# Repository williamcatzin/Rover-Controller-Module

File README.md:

# **Rover Controller Module**

The Rover Controller Module is an electronic control module (ECM) for a Mars rover prototype being developed by the AI Rover team from the Space Technologies At Cal (STAC). The PCB is a four-layer board consisting of an ESP32-WROOM32 module, BMI088 IMU breakout board, RFM69HCW transceiver module, UART header pin interface for three Roboclaw 2x7A motor controllers, and a SPI header pin interface for an external microprocessor such as an NVIDIA Jetson or Raspberry Pi. There’s also decoupling capacitors to suppress power supply noise and TVS diodes for safety and component protection. The PCB was designed using KiCAD and manufactured by JLCPCB. Top and bottom layers are signal planes. First middle layer is the ground plane and the second middle layer is the power plane. I've also placed three test points at the UART, I2C, and SPI serial buses respectively, mounting holes, and logos for aesthetics. Here’s the Rover Controller Module v1.

|||
|:-:|:-:|
|||

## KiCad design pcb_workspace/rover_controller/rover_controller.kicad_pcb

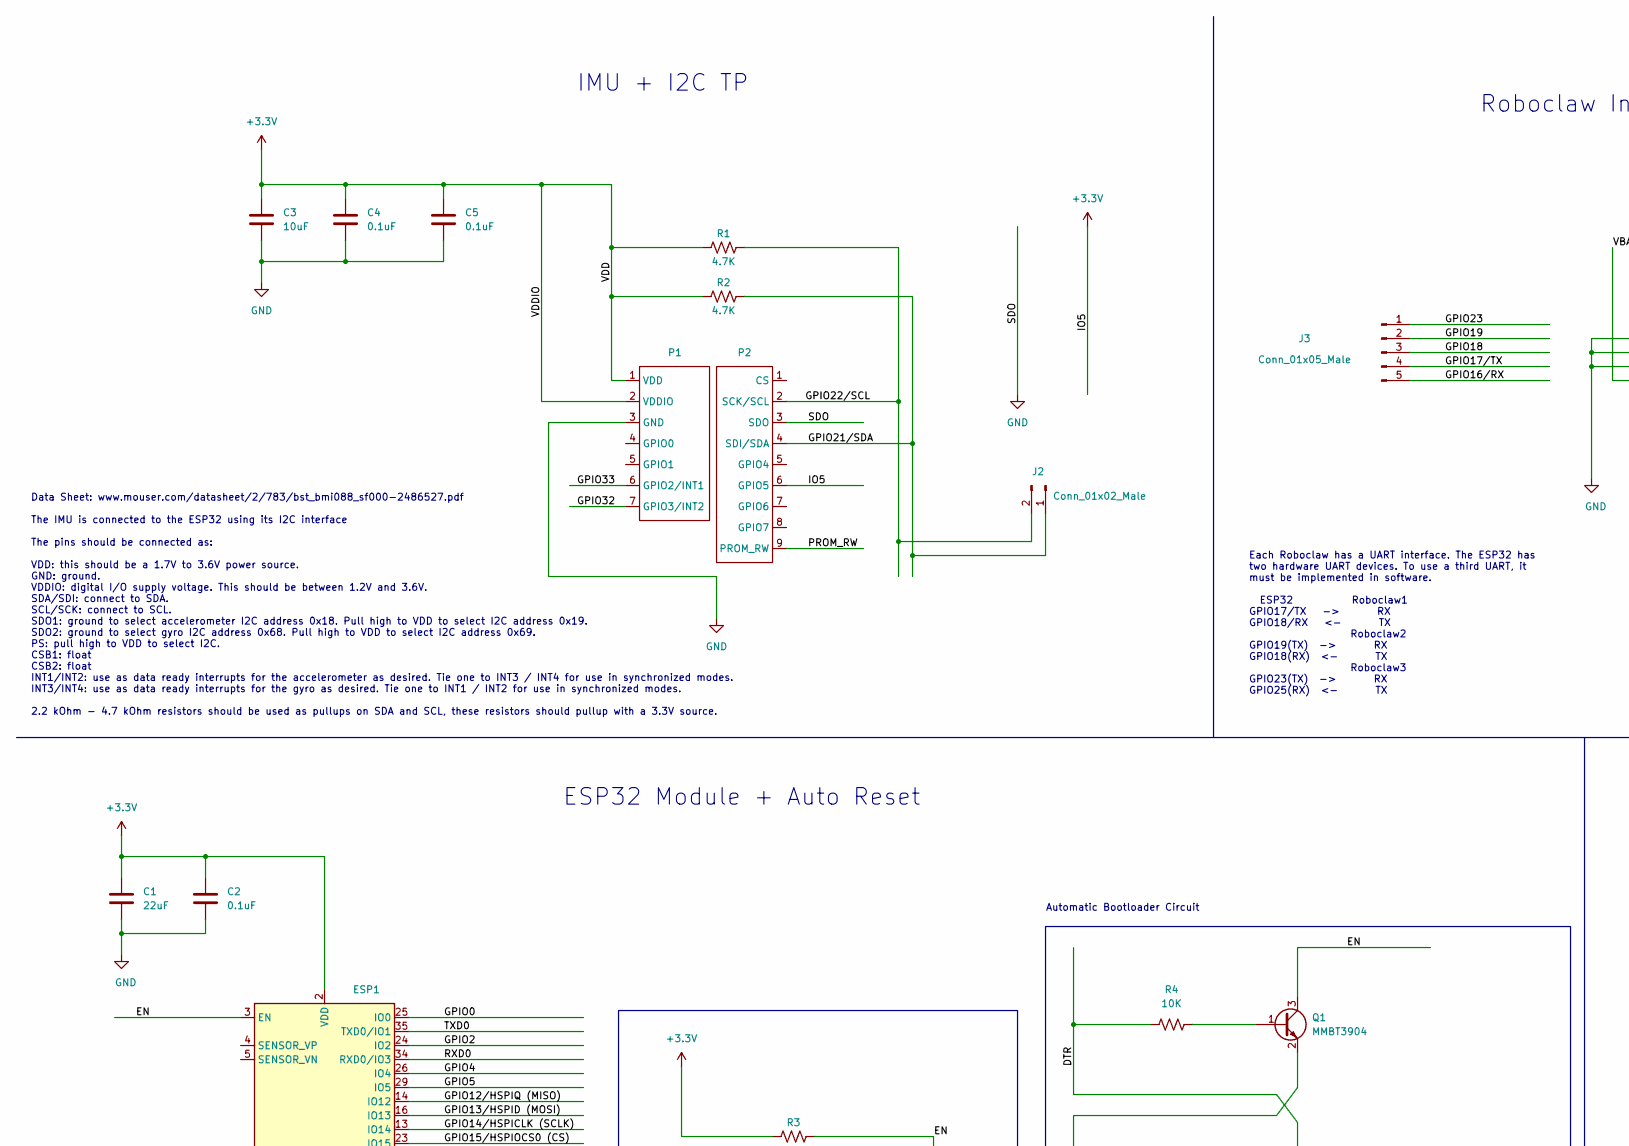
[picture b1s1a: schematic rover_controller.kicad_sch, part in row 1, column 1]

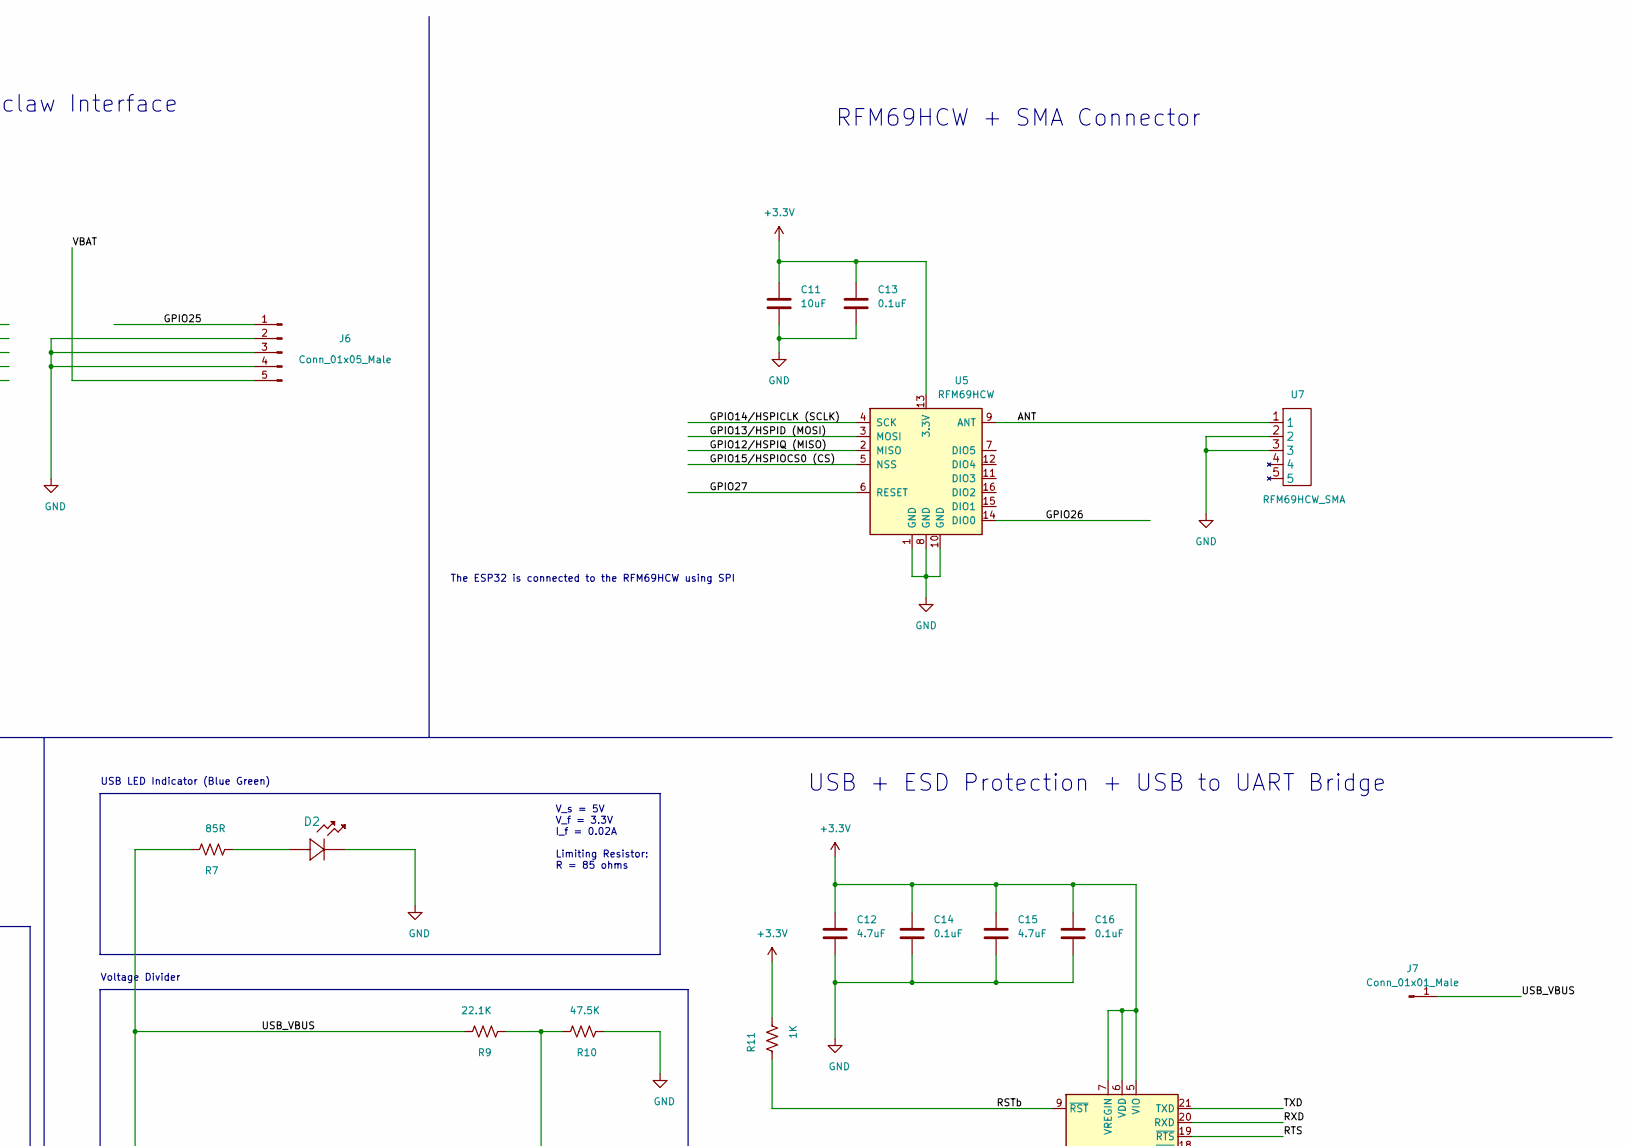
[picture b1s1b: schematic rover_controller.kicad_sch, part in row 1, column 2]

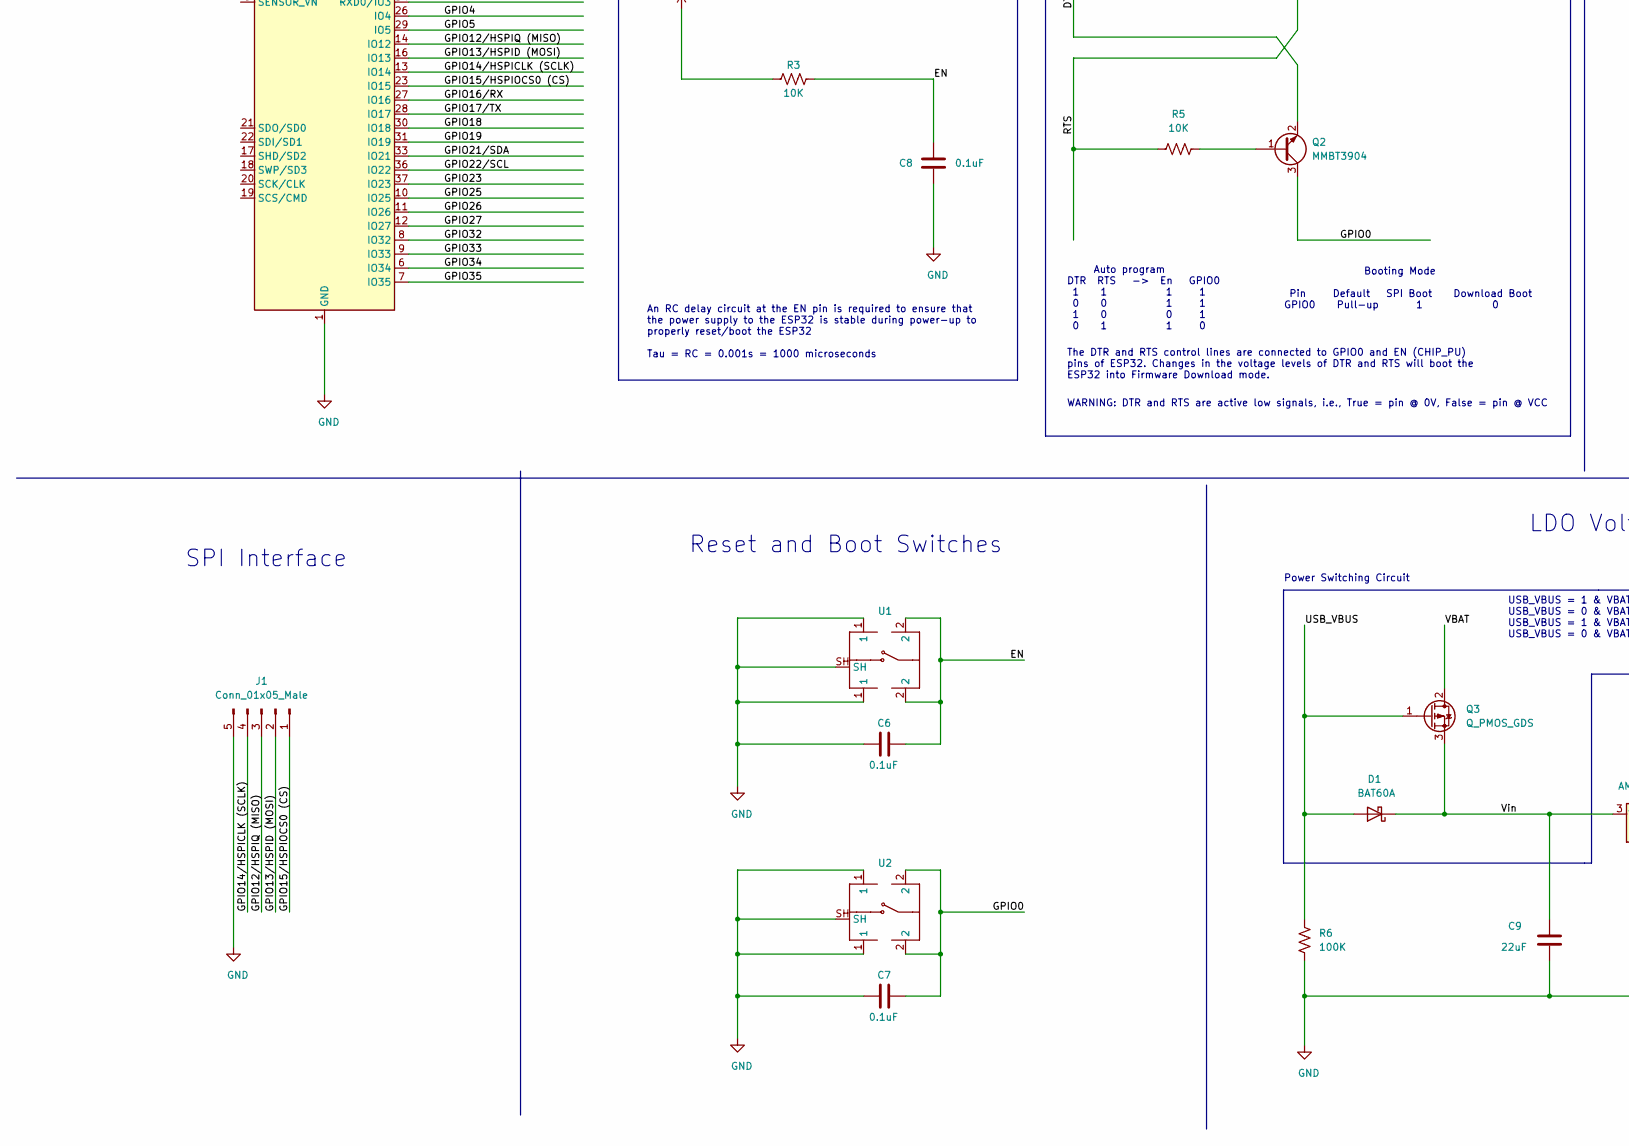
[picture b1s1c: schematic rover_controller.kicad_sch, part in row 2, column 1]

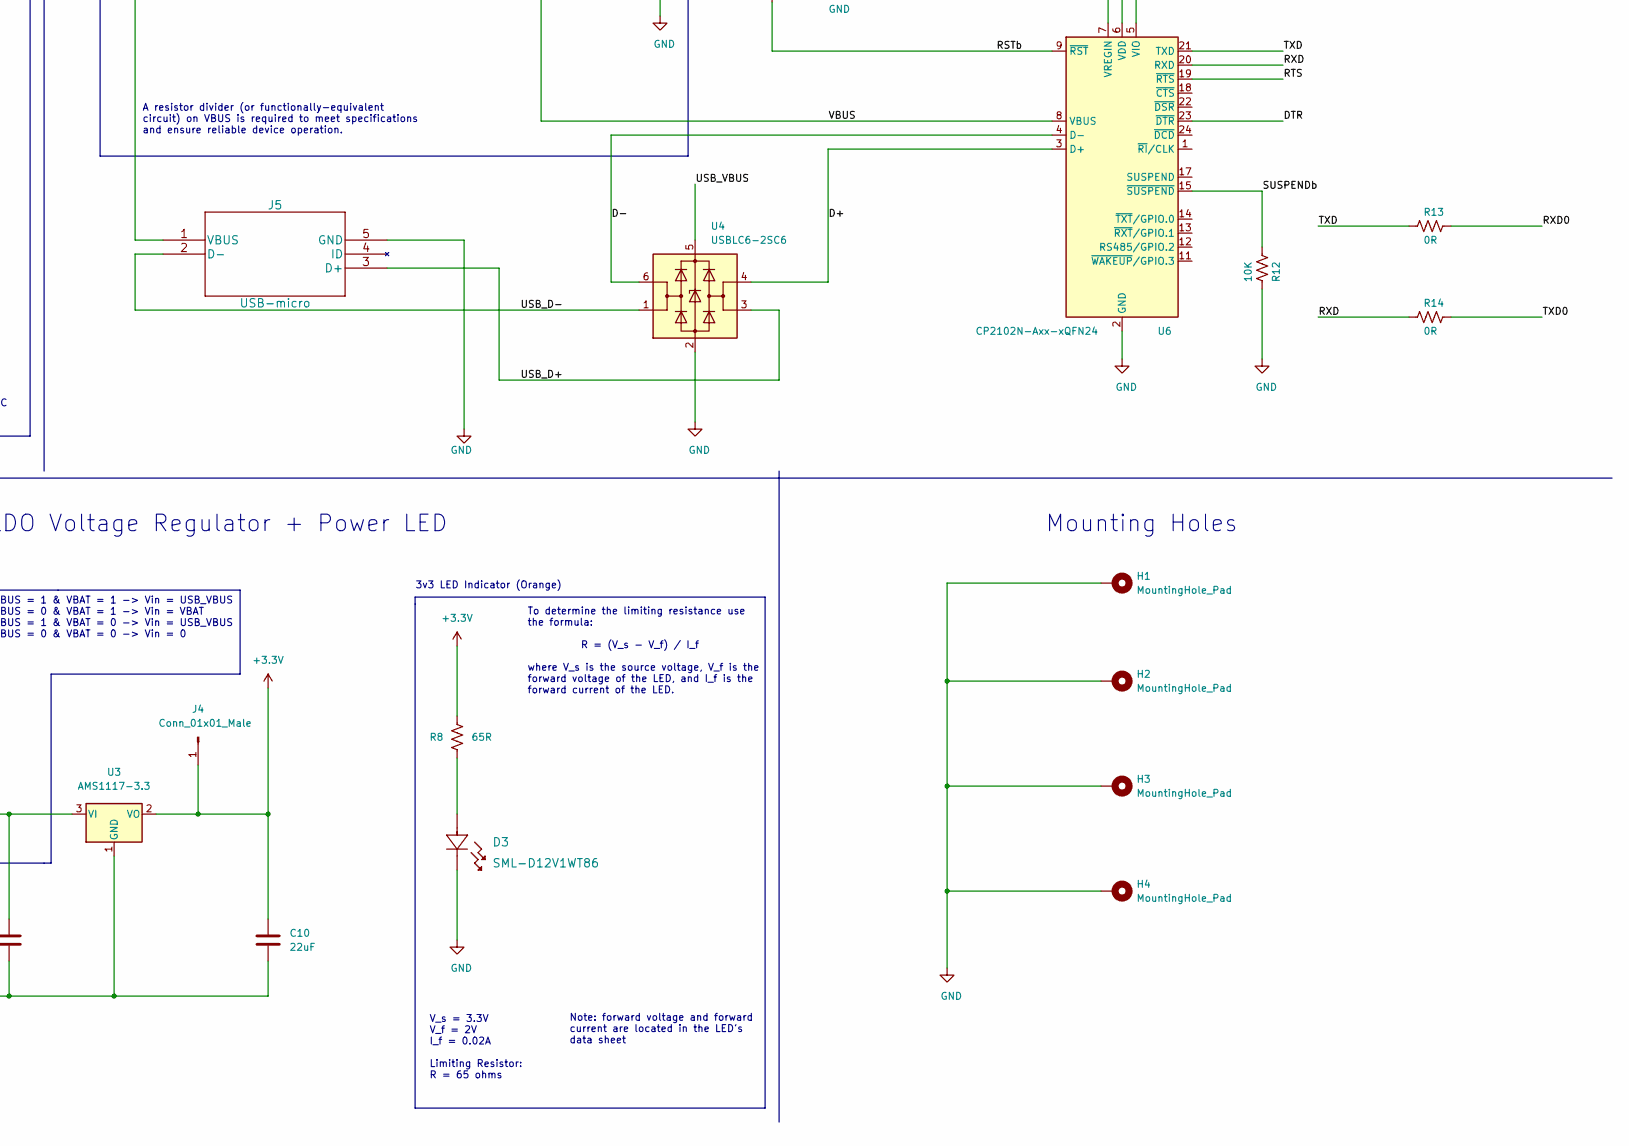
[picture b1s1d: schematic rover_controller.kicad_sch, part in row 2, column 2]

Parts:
C1: 22uF; C_0805_2012Metric_Pad1.18x1.45mm_HandSolder
C2, C4, C5, C6, C7, C8, C13: 0.1uF; C_0603_1608Metric_Pad1.08x0.95mm_HandSolder
C3, C11: 10uF; C_0805_2012Metric_Pad1.18x1.45mm_HandSolder
C9, C10: 22uF; C_1206_3216Metric_Pad1.33x1.80mm_HandSolder
C12, C15: 4.7uF; C_0603_1608Metric_Pad1.08x0.95mm_HandSolder
C14, C16: 0.1uF; C_0402_1005Metric_Pad0.74x0.62mm_HandSolder
D1: BAT60A; D_SOD-323
D2, D3: SML-D12V1WT86; LED_0603_1608Metric_Pad1.05x0.95mm_HandSolder
ESP1: ESP32-WROOM-32
H1, H2, H3, H4: MountingHole_Pad; MountingHole_4.3mm_M4_Pad_Via
J1, J3, J6: Conn_01x05_Male; PinHeader_1x05_P2.54mm_Vertical
J2: Conn_01x02_Male; PinHeader_1x02_P2.54mm_Vertical
J4, J7: Conn_01x01_Male; PinHeader_1x01_P2.54mm_Vertical
J5: USB-micro; USB_Micro-B_Molex_47346-0001
P1: BST_Shuttleboard_Conn1; PinSocket_1x07_P1.27mm_Vertical
P2: BST_Shuttleboard_Conn2; PinSocket_1x09_P1.27mm_Vertical
Q1, Q2: MMBT3904; SOT-23
Q3: Q_PMOS_GDS; SOT-23
R1, R2: 4.7K; R_0603_1608Metric_Pad0.98x0.95mm_HandSolder
R3, R4, R5: 10K; R_0805_2012Metric_Pad1.20x1.40mm_HandSolder
R6: 100K; R_1206_3216Metric_Pad1.30x1.75mm_HandSolder
R7: 85R; R_0603_1608Metric_Pad0.98x0.95mm_HandSolder
R8: 65R; R_0603_1608Metric_Pad0.98x0.95mm_HandSolder
R9: 22.1K; R_0603_1608Metric_Pad0.98x0.95mm_HandSolder
R10: 47.5K; R_0603_1608Metric_Pad0.98x0.95mm_HandSolder
R11: 1K; R_0603_1608Metric_Pad0.98x0.95mm_HandSolder
R12: 10K; R_0603_1608Metric_Pad0.98x0.95mm_HandSolder
R13, R14: 0R; R_0603_1608Metric_Pad0.98x0.95mm_HandSolder
U1, U2: KMR_SW_SPST; SW_Push_1P1T-SH_NO_CK_KMR2xxG
U3: AMS1117-3.3; SOT-223-3_TabPin2
U4: USBLC6-2SC6; SOT-23-6
U5: RFM69HCW
U6: CP2102N-Axx-xQFN24; QFN-24-1EP_4x4mm_P0.5mm_EP2.6x2.6mm
U7: RFM69HCW_SMA; 60312202114509

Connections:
+3V3: C1.1, C2.1, C3.1, C4.1, C5.1, C10.1, C11.1, C12.1, C13.1, C14.1, C15.1, C16.1, ESP1.2 (VDD), J4.1, P1.1 (VDD), P1.2 (VDDIO), P2.6 (GPIO5), R1.1, R2.1, R3.1, R8.1, R11.2, U3.2 (VO), U5.13 (3.3V), U6.5 (VIO), U6.6 (VDD), U6.7 (VREGIN)
/ANT: U5.9 (ANT), U7.1
/D+: U4.4 (I/O2), U6.3 (D+)
/D-: U4.6 (I/O1), U6.4 (D-)
/DTR: Q2.2 (E), R4.1, U6.23 (~DTR)
/EN: C6.2, C8.1, ESP1.3 (EN), Q1.3 (C), R3.2, U1.2
/GPIO0: C7.2, ESP1.25 (IO0), Q2.3 (C), U2.2
/GPIO2: ESP1.24 (IO2)
/GPIO4: ESP1.26 (IO4)
/GPIO5: ESP1.29 (IO5)
/GPIO12/HSPIQ (MISO): ESP1.14 (IO12), J1.3, U5.2 (MISO)
/GPIO13/HSPID (MOSI): ESP1.16 (IO13), J1.2, U5.3 (MOSI)
/GPIO14/HSPICLK (SCLK): ESP1.13 (IO14), J1.4, U5.4 (SCK)
/GPIO15/HSPIOCS0 (CS): ESP1.23 (IO15), J1.1, U5.5 (NSS)
/GPIO16/RX: ESP1.27 (IO16), J3.5
/GPIO17/TX: ESP1.28 (IO17), J3.4
/GPIO18: ESP1.30 (IO18), J3.3
/GPIO19: ESP1.31 (IO19), J3.2
/GPIO21/SDA: ESP1.33 (IO21), J2.1, P2.4 (SDI/SDA), R2.2
/GPIO22/SCL: ESP1.36 (IO22), J2.2, P2.2 (SCK/SCL), R1.2
/GPIO23: ESP1.37 (IO23), J3.1
/GPIO25: ESP1.10 (IO25), J6.1
/GPIO26: ESP1.11 (IO26), U5.14 (DIO0)
/GPIO27: ESP1.12 (IO27), U5.6 (RESET)
/GPIO32: ESP1.8 (IO32), P1.7 (GPIO3/INT2)
/GPIO33: ESP1.9 (IO33), P1.6 (GPIO2/INT1)
/GPIO34: ESP1.6 (IO34)
/GPIO35: ESP1.7 (IO35)
/PROM_RW: P2.9 (PROM_RW)
/RSTb: R11.1, U6.9 (~RST)
/RTS: Q1.2 (E), R5.1, U6.19 (~RTS)
/RXD: R14.2, U6.20 (RXD)
/RXD0: ESP1.34 (RXD0/IO3), R13.1
/SUSPENDb: R12.2, U6.15 (~SUSPEND)
/TXD: R13.2, U6.21 (TXD)
/TXD0: ESP1.35 (TXD0/IO1), R14.1
/USB_D+: J5.3 (D+), U4.3 (I/O2)
/USB_D-: J5.2 (D-), U4.1 (I/O1)
/USB_VBUS: D1.2 (A), J5.1 (VBUS), J7.1, Q3.1 (G), R6.1, R7.1, R9.1, U4.5 (VBUS)
/VBAT: J6.5, Q3.2 (D)
/VBUS: R9.2, R10.2, U6.8 (VBUS)
/Vin: C9.1, D1.1 (K), Q3.3 (S), U3.3 (VI)
GND: C1.2, C2.2, C3.2, C4.2, C5.2, C6.1, C7.1, C8.2, C9.2, C10.2, C11.2, C12.2, C13.2, C14.2, C15.2, C16.2, D2.1, D3.1, ESP1.1 (GND), ESP1.15 (GND), ESP1.38 (GND), ESP1.39 (GND), H1.1, H2.1, H3.1, H4.1, J1.5, J5.5 (GND), J6.2, J6.3, J6.4, P1.3 (GND), P2.3 (SDO), R6.2, R10.1, R12.1, U1.1, U1.SH, U2.1, U2.SH, U3.1 (GND), U4.2 (GND), U5.1 (GND), U5.8 (GND), U5.10 (GND), U6.2 (GND), U6.25 (GND), U7.2, U7.3
unnamed: D2.2, R7.2
unnamed: D3.2, R8.2
unnamed: Q1.1 (B), R4.2
unnamed: Q2.1 (B), R5.2

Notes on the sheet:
SPI Interface
3v3 LED Indicator (Orange)
Each Roboclaw has a UART interface. The ESP32 has two hardware UART devices. To use a third UART, it must be implemented in software. ESP32 Roboclaw1 GPIO17/TX -> RX GPIO18/RX <- TX Roboclaw2 GPIO19(TX) -> RX GPIO18(RX) <- TX Roboclaw3 GPIO23(TX) -> RX GPIO25(RX) <- TX
Note: forward voltage and forward current are located in the LED's data sheet
An RC delay circuit at the EN pin is required to ensure that the power supply to the ESP32 is stable during power-up to properly reset/boot the ESP32 Tau = RC = 0.001s = 1000 microseconds
The ESP32 is connected to the RFM69HCW using SPI
Power Switching Circuit
A resistor divider (or functionally-equivalent circuit) on VBUS is required to meet specifications and ensure reliable device operation.
Mounting Holes
IMU + I2C TP
WARNING: DTR and RTS are active low signals, i.e., True = pin @ 0V, False = pin @ VCC
USB + ESD Protection + USB to UART Bridge
USB_VBUS = 1 & VBAT = 1 -> Vin = USB_VBUS USB_VBUS = 0 & VBAT = 1 -> Vin = VBAT USB_VBUS = 1 & VBAT = 0 -> Vin = USB_VBUS USB_VBUS = 0 & VBAT = 0 -> Vin = 0
The DTR and RTS control lines are connected to GPIO0 and EN (CHIP_PU) pins of ESP32. Changes in the voltage levels of DTR and RTS will boot the ESP32 into Firmware Download mode.
RFM69HCW + SMA Connector
LDO Voltage Regulator + Power LED
V_s = 5V V_f = 3.3V I_f = 0.02A Limiting Resistor: R = 85 ohms
To determine the limiting resistance use the formula: R = (V_s - V_f) / I_f where V_s is the source voltage, V_f is the forward voltage of the LED, and I_f is the forward current of the LED.
Booting Mode Pin Default SPI Boot Download Boot GPIO0 Pull-up 1 0
Auto program DTR RTS -> En GPIO0 1 1 1 1 0 0 1 1 1 0 0 1 0 1 1 0
Automatic Bootloader Circuit
Roboclaw Interface
Voltage Divider
ESP32 Module + Auto Reset
Reset and Boot Switches
USB LED Indicator (Blue Green)
V_s = 3.3V V_f = 2V I_f = 0.02A Limiting Resistor: R = 65 ohms
Data Sheet: www.mouser.com/datasheet/2/783/bst_bmi088_sf000-2486527.pdf The IMU is connected to the ESP32 using its I2C interface The pins should be connected as: VDD: this should be a 1.7V to 3.6V power source. GND: ground. VDDIO: digital I/O supply voltage. This should be between 1.2V and 3.6V. S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

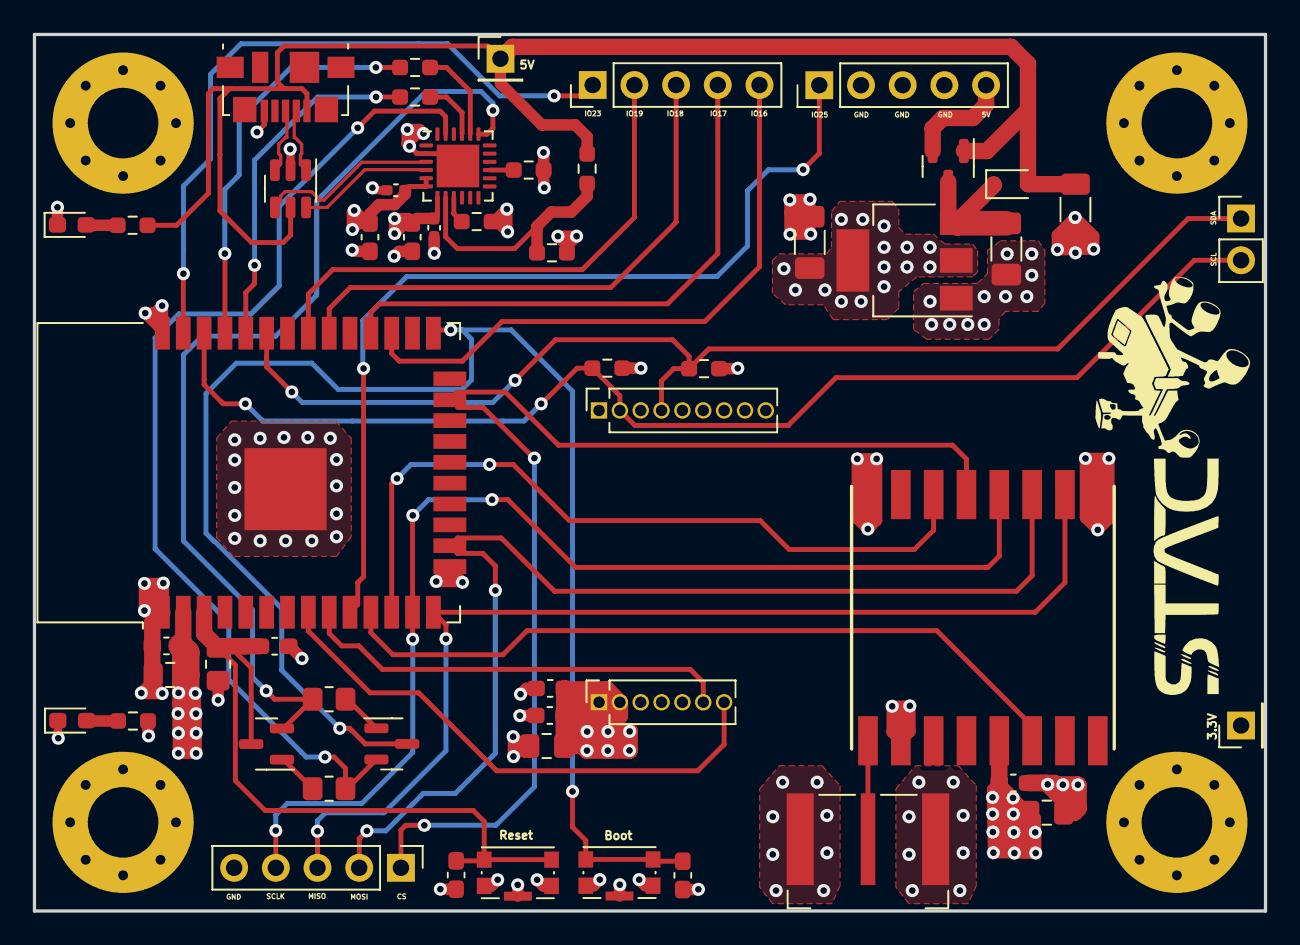
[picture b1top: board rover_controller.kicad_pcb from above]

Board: 4 copper layers, 75.0 x 53.4 mm, 57 parts (0 on the bottom side), 41 nets.

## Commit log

2022-08-29 First push
2022-09-21 Created README doc
